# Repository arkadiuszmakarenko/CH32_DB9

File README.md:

Work in progress.

USB HID to DB9 Adapter
It has been desigend for dual use, but primarily for MSX computers.

Current support:
- MSX Gamepad

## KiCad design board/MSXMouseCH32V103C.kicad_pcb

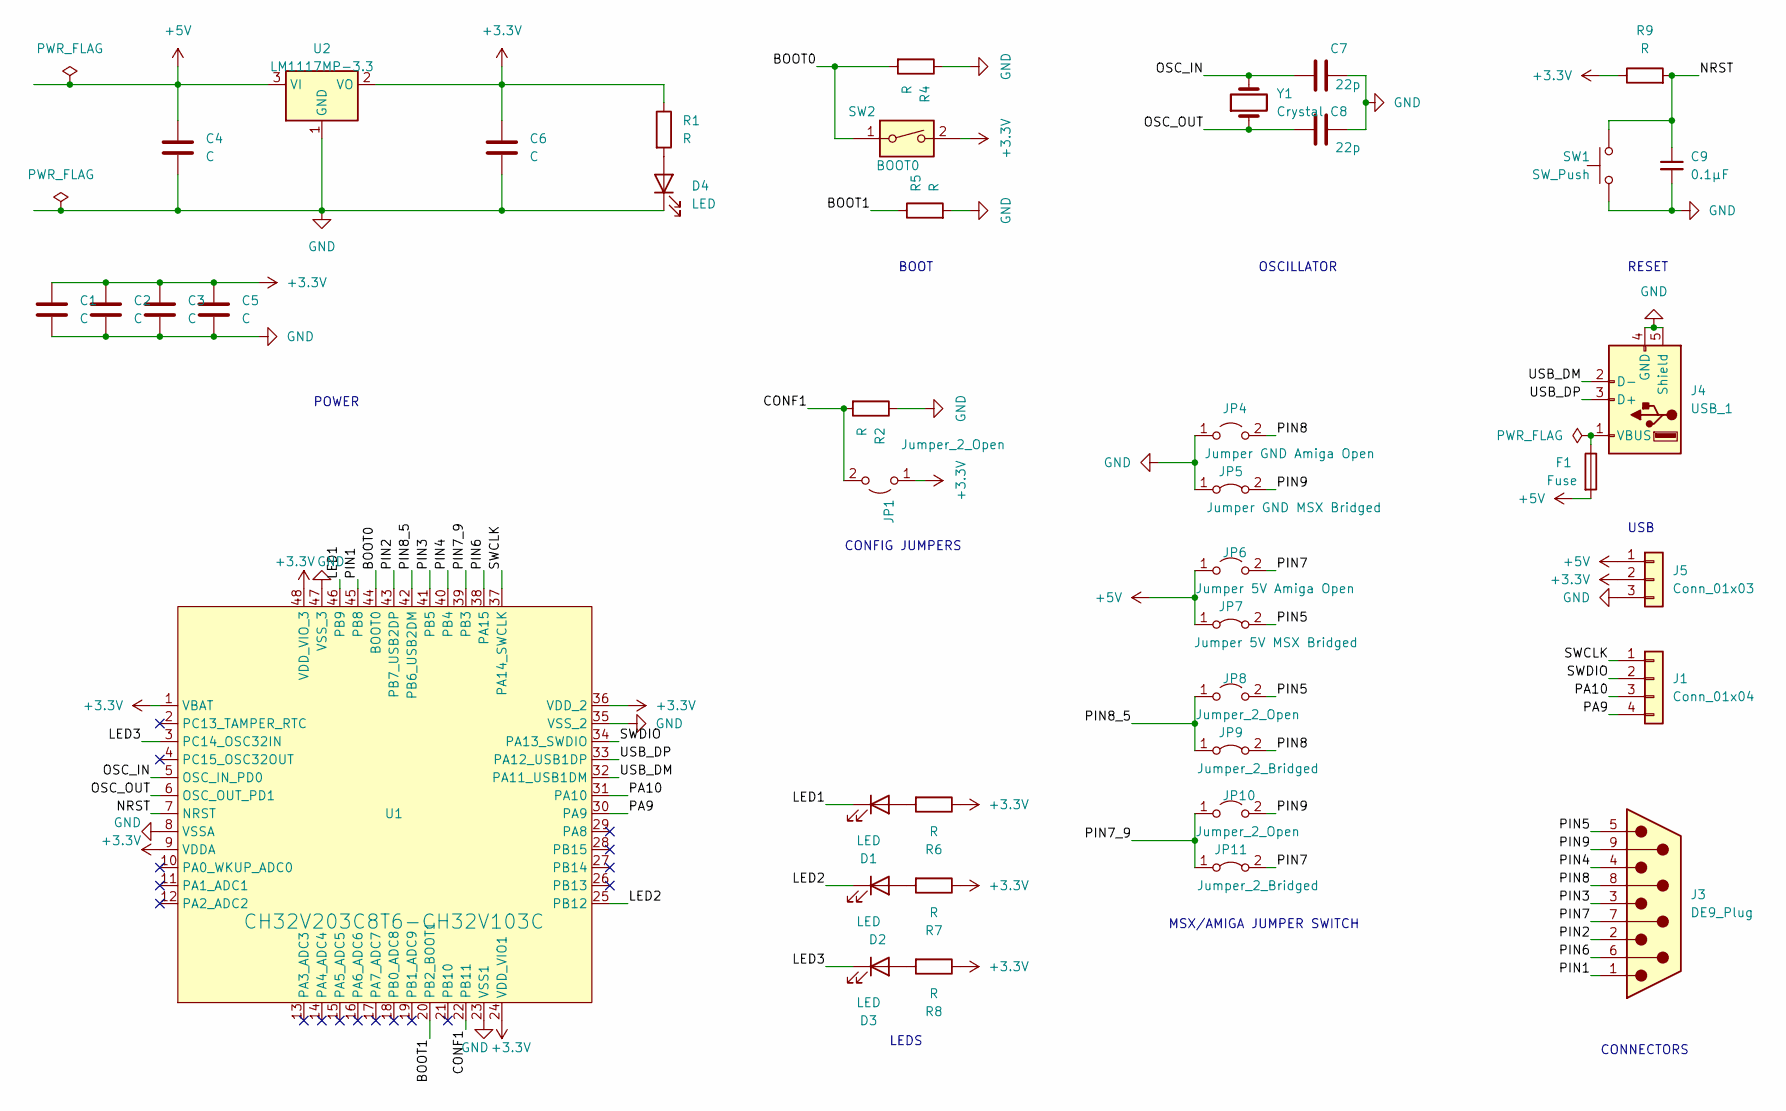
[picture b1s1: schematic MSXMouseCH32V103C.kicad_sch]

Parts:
C1, C2, C3, C4, C5, C6: C; C_0805_2012Metric_Pad1.18x1.45mm_HandSolder
C7, C8: 22p; C_0805_2012Metric_Pad1.18x1.45mm_HandSolder
C9: 0.1μF; C_0603_1608Metric; LCSC C14663
D1, D2, D3, D4: LED; LED_0805_2012Metric_Pad1.15x1.40mm_HandSolder
F1: Fuse; Fuse_1206_3216Metric_Pad1.42x1.75mm_HandSolder
J1: Conn_01x04; PinHeader_1x04_P2.54mm_Vertical
J3: DE9_Plug; DSUB-9_Female_EdgeMount_P2.77mm
J4: USB_1; USB_A_CONNFLY_DS1095-WNR0
J5: Conn_01x03; PinHeader_1x03_P2.54mm_Vertical
JP1, JP8, JP10: Jumper_2_Open; SolderJumper-2_P1.3mm_Open_RoundedPad1.0x1.5mm
JP4: Jumper GND Amiga Open; SolderJumper-2_P1.3mm_Open_RoundedPad1.0x1.5mm
JP5: Jumper GND MSX Bridged; SolderJumper-2_P1.3mm_Bridged_RoundedPad1.0x1.5mm
JP6: Jumper 5V Amiga Open; SolderJumper-2_P1.3mm_Open_RoundedPad1.0x1.5mm
JP7: Jumper 5V MSX Bridged; SolderJumper-2_P1.3mm_Bridged_RoundedPad1.0x1.5mm
JP9, JP11: Jumper_2_Bridged; SolderJumper-2_P1.3mm_Bridged_RoundedPad1.0x1.5mm
R1, R2, R4, R5, R6, R7, R8, R9: R; R_0805_2012Metric_Pad1.20x1.40mm_HandSolder
SW1: SW_Push; PinSocket_1x02_P2.54mm_Vertical; LCSC C2888884
SW2: BOOT0; PinHeader_1x02_P2.54mm_Vertical
U1: CH32V203C8T6-CH32V103C; CH32V203C8T6_LQFP-48_7x7mm_P0.5mm
U2: LM1117MP-3.3; SOT-223-3_TabPin2
Y1: Crystal; Crystal_HC49-U_Vertical

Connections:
+3.3V: C1.1, C2.1, C3.1, C5.1, C6.1, J5.2, JP1.1 (A), R1.1, R6.1, R7.1, R8.1, R9.1, SW2.2, U1.1 (VBAT), U1.9 (VDDA), U1.24 (VDD_VIO1), U1.36 (VDD_2), U1.48 (VDD_VIO_3), U2.2 (VO)
+5V: C4.1, F1.2, J5.1, JP6.1 (A), JP7.1 (A), U2.3 (VI)
/BOOT0: R4.2, SW2.1, U1.44 (BOOT0)
/BOOT1: R5.1, U1.20 (PB2_BOOT1)
/CONF1: JP1.2 (B), R2.2, U1.22 (PB11)
/LED1: D1.1 (K), U1.46 (PB9)
/LED2: D2.1 (K), U1.25 (PB12)
/LED3: D3.1 (K), U1.3 (PC14_OSC32IN)
/NRST: C9.1, R9.2, SW1.2, U1.7 (NRST)
/OSC_IN: C7.1, U1.5 (OSC_IN_PD0), Y1.2
/OSC_OUT: C8.1, U1.6 (OSC_OUT_PD1), Y1.1
/PA9: J1.4, U1.30 (PA9)
/PA10: J1.3, U1.31 (PA10)
/PIN1: J3.1, U1.45 (PB8)
/PIN2: J3.2, U1.43 (PB7_USB2DP)
/PIN3: J3.3, U1.41 (PB5)
/PIN4: J3.4, U1.40 (PB4)
/PIN5: J3.5, JP7.2 (B), JP8.2 (B)
/PIN6: J3.6, U1.38 (PA15)
/PIN7: J3.7, JP6.2 (B), JP11.2 (B)
/PIN7_9: JP10.1 (A), JP11.1 (A), U1.39 (PB3)
/PIN8: J3.8, JP4.2 (B), JP9.2 (B)
/PIN8_5: JP8.1 (A), JP9.1 (A), U1.42 (PB6_USB2DM)
/PIN9: J3.9, JP5.2 (B), JP10.2 (B)
/SWCLK: J1.1, U1.37 (PA14_SWCLK)
/SWDIO: J1.2, U1.34 (PA13_SWDIO)
/USB_DM: J4.2 (D-), U1.32 (PA11_USB1DM)
/USB_DP: J4.3 (D+), U1.33 (PA12_USB1DP)
GND: C1.2, C2.2, C3.2, C4.2, C5.2, C6.2, C7.2, C8.2, C9.2, D4.1 (K), J4.4 (GND), J4.5 (Shield), J5.3, JP4.1 (A), JP5.1 (A), R2.1, R4.1, R5.2, SW1.1, U1.8 (VSSA), U1.23 (VSS1), U1.35 (VSS_2), U1.47 (VSS_3), U2.1 (GND)
unnamed: D1.2 (A), R6.2
unnamed: D2.2 (A), R7.2
unnamed: D3.2 (A), R8.2
unnamed: D4.2 (A), R1.2
unnamed: F1.1, J4.1 (VBUS)

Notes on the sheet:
CONNECTORS
CONFIG JUMPERS
OSCILLATOR
LEDS
MSX/AMIGA JUMPER SWITCH
USB
BOOT
POWER
RESET

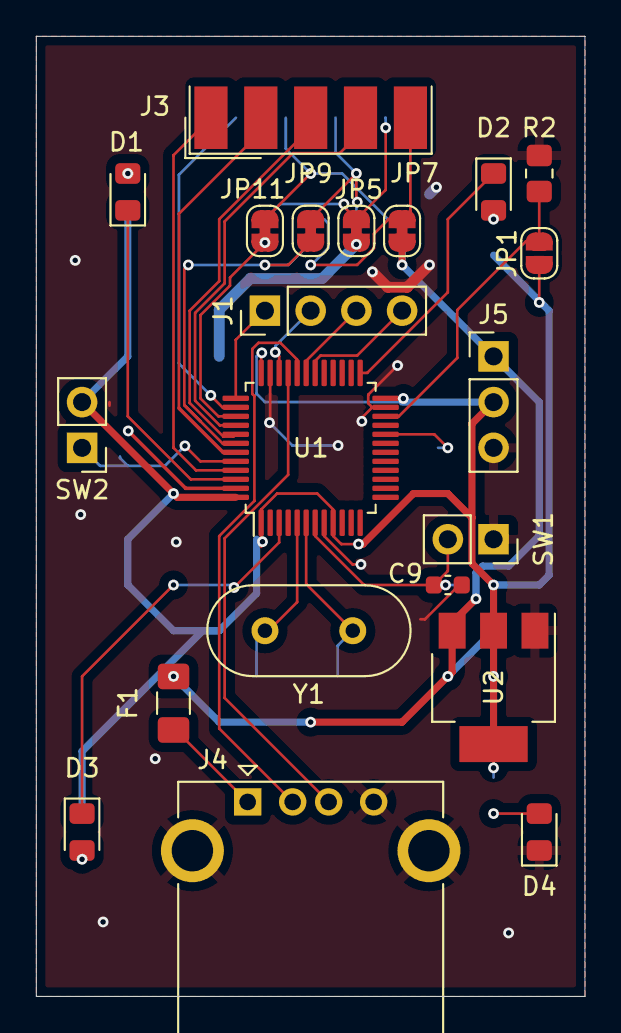
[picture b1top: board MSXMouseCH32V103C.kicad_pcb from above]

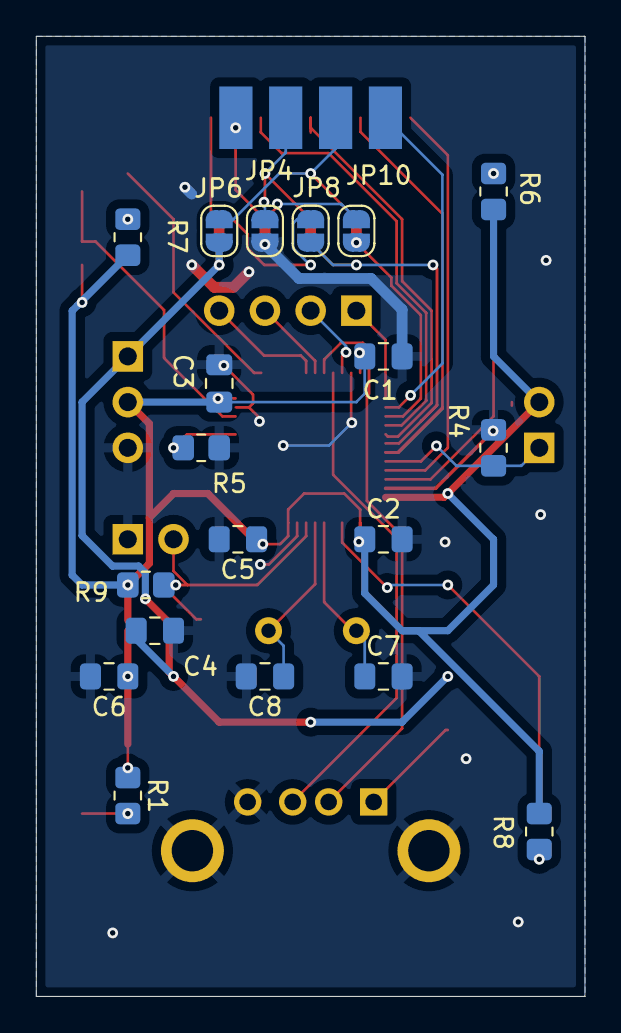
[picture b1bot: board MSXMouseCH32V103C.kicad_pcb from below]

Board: 2 copper layers, 30.5 x 53.3 mm, 40 parts (19 on the bottom side), 34 nets.

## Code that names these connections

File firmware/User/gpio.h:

#ifndef __GPIO_H
#define __GPIO_H

#include "ch32v10x_gpio.h"

//CONFIG
#define CONFIG1_Pin GPIO_Pin_11
#define CONFIG1_GPIO_Port GPIOB


//LEDs
#define LED1_Pin GPIO_Pin_9
#define LED1_GPIO_Port GPIOB

#define LED2_Pin GPIO_Pin_12
#define LED2_GPIO_Port GPIOB

#define LED3_Pin GPIO_Pin_14
#define LED3_GPIO_Port GPIOC



//BUTTONS
#define RB_Pin GPIO_Pin_3
#define RB_GPIO_Port GPIOB

#define MB_Pin GPIO_Pin_6
#define MB_GPIO_Port GPIOB

#define LB_Pin GPIO_Pin_15
#define LB_GPIO_Port GPIOA

//DIRECTIONS
#define RHQ_Pin GPIO_Pin_4
#define RHQ_GPIO_Port GPIOB

#define LVQ_Pin GPIO_Pin_5
#define LVQ_GPIO_Port GPIOB

#define BH_Pin GPIO_Pin_7
#define BH_GPIO_Port GPIOB

#define FV_Pin GPIO_Pin_8
#define FV_GPIO_Port GPIOB

//DB9 PIN

#define PIN1_Pin GPIO_Pin_8
#define PIN1_GPIO_Port GPIOB

#define PIN2_Pin GPIO_Pin_7
#define PIN2_GPIO_Port GPIOB

#define PIN3_Pin GPIO_Pin_5
#define PIN3_GPIO_Port GPIOB

#define PIN4_Pin GPIO_Pin_4
#define PIN4_GPIO_Port GPIOB

#define PIN85_Pin GPIO_Pin_6
#define PIN85_GPIO_Port GPIOB

#define PIN79_Pin GPIO_Pin_3
#define PIN79_GPIO_Port GPIOB

#define PIN6_Pin GPIO_Pin_15
#define PIN6_GPIO_Port GPIOA










void GPIO_Config();


#endif

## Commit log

2023-12-16 Project Rename
2023-12-16 Project restructure
2023-12-16 Rename and project tidy up Initial empty firmware setup
2023-12-17 Mouse, joypad and keyboard decoding Hub managment
2023-12-19 MSX Gamepad implemented
